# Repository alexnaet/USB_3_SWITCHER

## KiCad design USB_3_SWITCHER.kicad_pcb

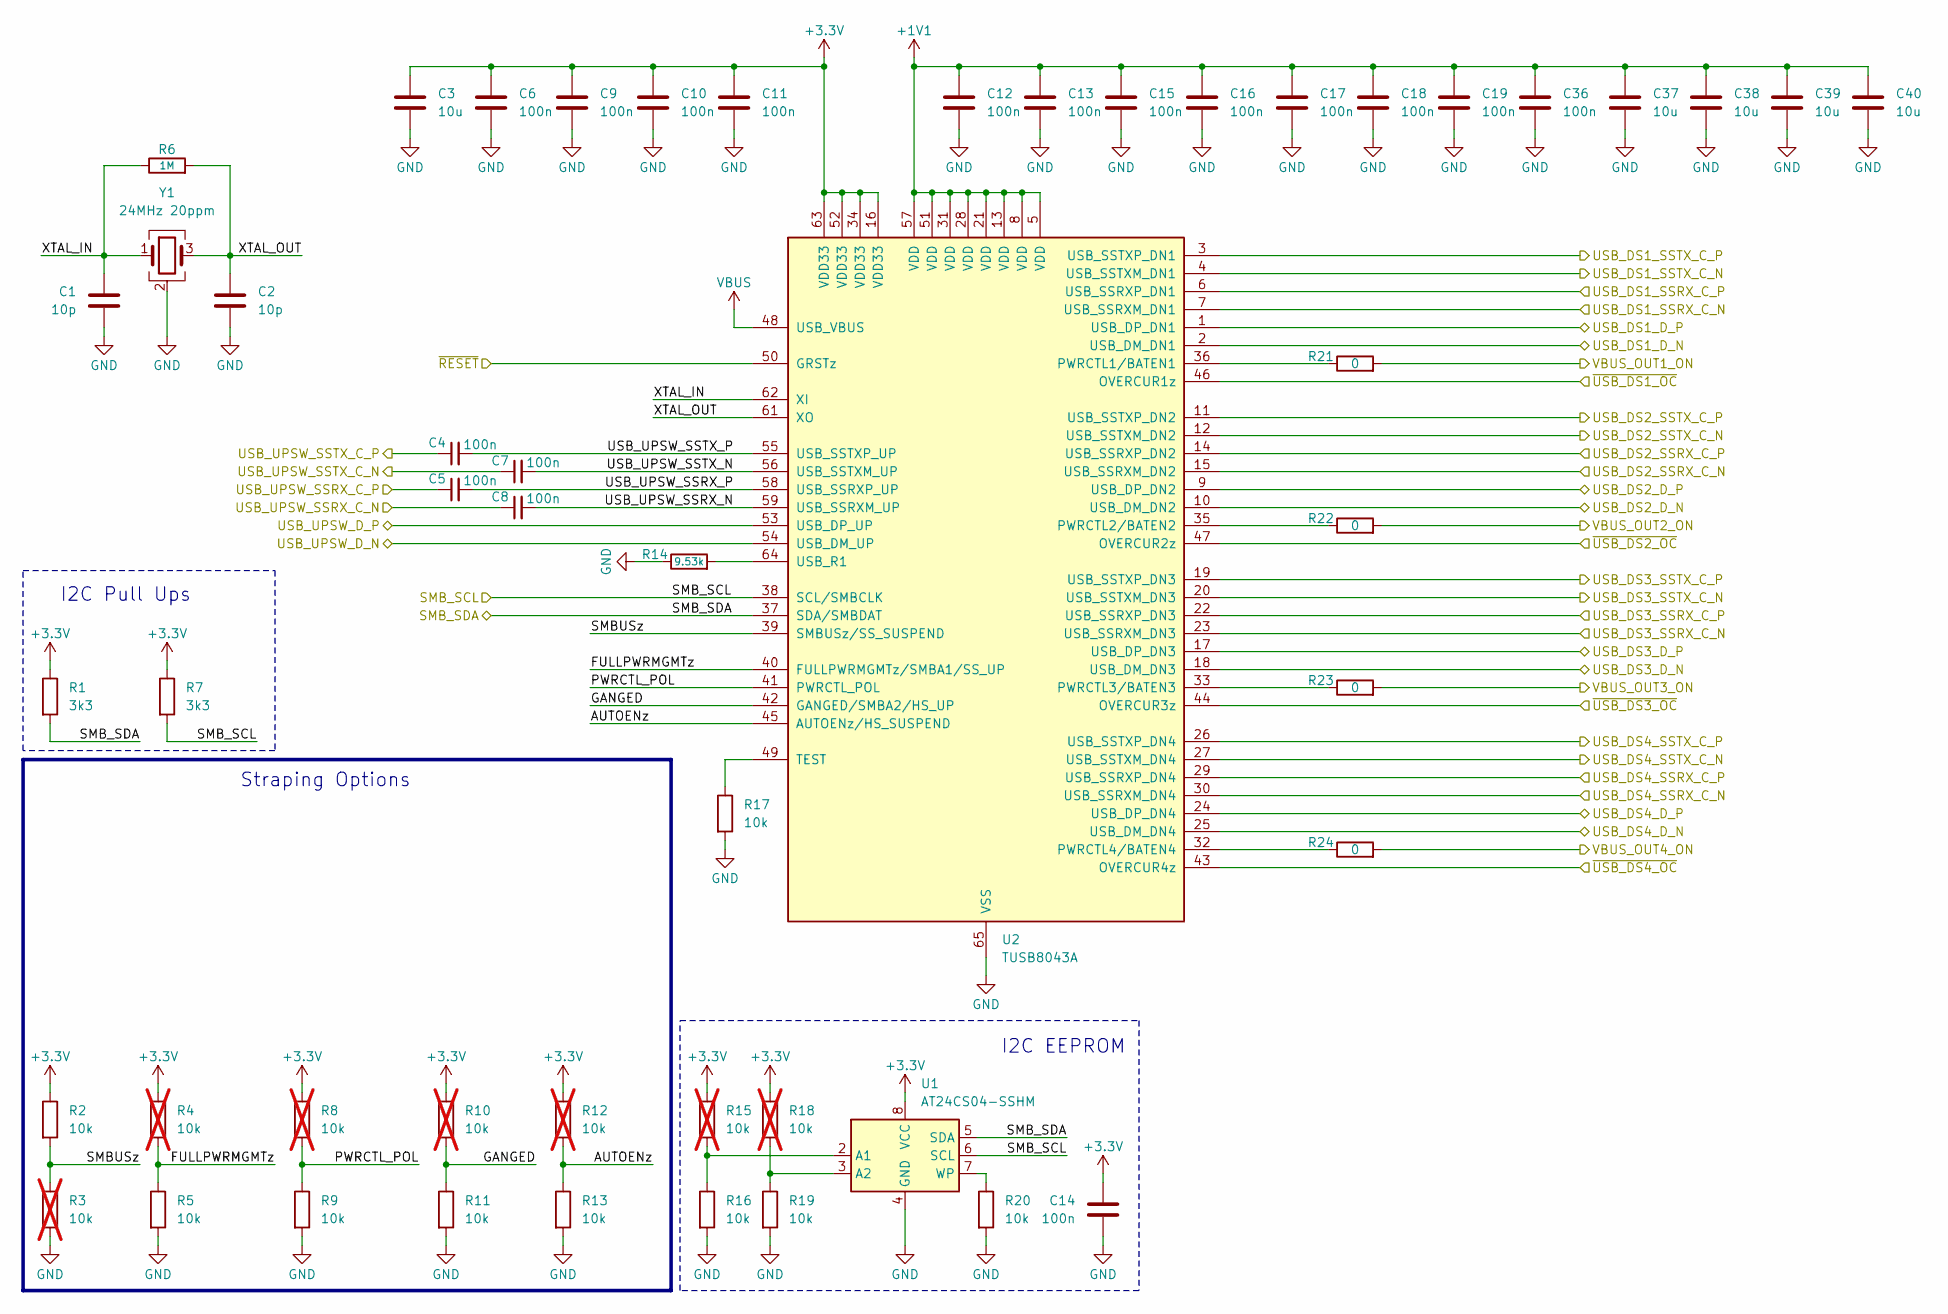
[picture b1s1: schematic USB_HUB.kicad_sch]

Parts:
C1, C2: 10p; Cap_0402
C3, C37, C38, C39, C40: 10u; Cap_0603
C4, C5, C6, C7, C8, C9, C10, C11, C12, C13, C14, C15, C16, C17, C18, C19, C36: 100n; Cap_0402
R1, R7: 3k3; Res_0402
R2, R5, R9, R11, R13, R16, R17, R19, R20: 10k; Res_0402
R3, R4, R8, R10, R12, R15, R18: 10k; Res_0402; not fitted
R6: 1M; Res_0402
R14: 9.53k; Res_0402
R21, R22, R23, R24: 0; Res_0402
U1: AT24CS04-SSHM; SOIC-8_3.9x4.9mm_P1.27mm
U2: TUSB8043A; QFN-64-1EP_9x9mm_P0.5mm_EP6x6mm_ThermalVias
Y1: 24MHz 20ppm; Crystal_SMD_3225-4Pin_3.2x2.5mm

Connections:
+1V1: C12.2, C13.2, C15.2, C16.2, C17.2, C18.2, C19.2, C36.2, C37.1, C38.1, C39.1, C40.1, U2.5 (VDD), U2.8 (VDD), U2.13 (VDD), U2.21 (VDD), U2.28 (VDD), U2.31 (VDD), U2.51 (VDD), U2.57 (VDD); also elsewhere on the board
+3.3V: C3.1, C6.2, C9.2, C10.2, C11.2, C14.2, R1.1, R2.1, R4.1, R7.1, R8.1, R10.1, R12.1, R15.1, R18.1, U1.8 (VCC), U2.16 (VDD33), U2.34 (VDD33), U2.52 (VDD33), U2.63 (VDD33); also elsewhere on the board
/DIRECTION_SWITCH/~RESET: U2.50 (GRSTz); also elsewhere on the board
/DOWNSTREAM_CONNECTORS1/USB_DS_D_N: U2.10 (USB_DM_DN2); also elsewhere on the board
/DOWNSTREAM_CONNECTORS1/USB_DS_D_P: U2.9 (USB_DP_DN2); also elsewhere on the board
/DOWNSTREAM_CONNECTORS1/USB_DS_SSRX_C_N: U2.15 (USB_SSRXM_DN2); also elsewhere on the board
/DOWNSTREAM_CONNECTORS1/USB_DS_SSRX_C_P: U2.14 (USB_SSRXP_DN2); also elsewhere on the board
/DOWNSTREAM_CONNECTORS1/USB_DS_SSTX_C_N: U2.12 (USB_SSTXM_DN2); also elsewhere on the board
/DOWNSTREAM_CONNECTORS1/USB_DS_SSTX_C_P: U2.11 (USB_SSTXP_DN2); also elsewhere on the board
/DOWNSTREAM_CONNECTORS1/VBUS_OUT_ON: R22.2; also elsewhere on the board
/DOWNSTREAM_CONNECTORS1/~USB_DS_OC: U2.47 (OVERCUR2z); also elsewhere on the board
/DOWNSTREAM_CONNECTORS2/USB_DS_D_N: U2.18 (USB_DM_DN3); also elsewhere on the board
/DOWNSTREAM_CONNECTORS2/USB_DS_D_P: U2.17 (USB_DP_DN3); also elsewhere on the board
/DOWNSTREAM_CONNECTORS2/USB_DS_SSRX_C_N: U2.23 (USB_SSRXM_DN3); also elsewhere on the board
/DOWNSTREAM_CONNECTORS2/USB_DS_SSRX_C_P: U2.22 (USB_SSRXP_DN3); also elsewhere on the board
/DOWNSTREAM_CONNECTORS2/USB_DS_SSTX_C_N: U2.20 (USB_SSTXM_DN3); also elsewhere on the board
/DOWNSTREAM_CONNECTORS2/USB_DS_SSTX_C_P: U2.19 (USB_SSTXP_DN3); also elsewhere on the board
/DOWNSTREAM_CONNECTORS2/VBUS_OUT_ON: R23.2; also elsewhere on the board
/DOWNSTREAM_CONNECTORS2/~USB_DS_OC: U2.44 (OVERCUR3z); also elsewhere on the board
/DOWNSTREAM_CONNECTORS3/USB_DS_D_N: U2.25 (USB_DM_DN4); also elsewhere on the board
/DOWNSTREAM_CONNECTORS3/USB_DS_D_P: U2.24 (USB_DP_DN4); also elsewhere on the board
/DOWNSTREAM_CONNECTORS3/USB_DS_SSRX_C_N: U2.30 (USB_SSRXM_DN4); also elsewhere on the board
/DOWNSTREAM_CONNECTORS3/USB_DS_SSRX_C_P: U2.29 (USB_SSRXP_DN4); also elsewhere on the board
/DOWNSTREAM_CONNECTORS3/USB_DS_SSTX_C_N: U2.27 (USB_SSTXM_DN4); also elsewhere on the board
/DOWNSTREAM_CONNECTORS3/USB_DS_SSTX_C_P: U2.26 (USB_SSTXP_DN4); also elsewhere on the board
/DOWNSTREAM_CONNECTORS3/VBUS_OUT_ON: R24.2; also elsewhere on the board
/DOWNSTREAM_CONNECTORS3/~USB_DS_OC: U2.43 (OVERCUR4z); also elsewhere on the board
/DOWNSTREAM_CONNECTORS/USB_DS_D_N: U2.2 (USB_DM_DN1); also elsewhere on the board
/DOWNSTREAM_CONNECTORS/USB_DS_D_P: U2.1 (USB_DP_DN1); also elsewhere on the board
/DOWNSTREAM_CONNECTORS/USB_DS_SSRX_C_N: U2.7 (USB_SSRXM_DN1); also elsewhere on the board
/DOWNSTREAM_CONNECTORS/USB_DS_SSRX_C_P: U2.6 (USB_SSRXP_DN1); also elsewhere on the board
/DOWNSTREAM_CONNECTORS/USB_DS_SSTX_C_N: U2.4 (USB_SSTXM_DN1); also elsewhere on the board
/DOWNSTREAM_CONNECTORS/USB_DS_SSTX_C_P: U2.3 (USB_SSTXP_DN1); also elsewhere on the board
/DOWNSTREAM_CONNECTORS/VBUS_OUT_ON: R21.2; also elsewhere on the board
/DOWNSTREAM_CONNECTORS/~USB_DS_OC: U2.46 (OVERCUR1z); also elsewhere on the board
/HS_MUX/USB_UPSW_D_N: U2.54 (USB_DM_UP); also elsewhere on the board
/HS_MUX/USB_UPSW_D_P: U2.53 (USB_DP_UP); also elsewhere on the board
/HS_MUX/USB_UPSW_SSRX_C_N: C8.1; also elsewhere on the board
/HS_MUX/USB_UPSW_SSRX_C_P: C5.1; also elsewhere on the board
/HS_MUX/USB_UPSW_SSTX_C_N: C7.1; also elsewhere on the board
/HS_MUX/USB_UPSW_SSTX_C_P: C4.1; also elsewhere on the board
/USB_HUB/AUTOENz: R12.2, R13.1, U2.45 (AUTOENz/HS_SUSPEND)
/USB_HUB/FULLPWRMGMTz: R4.2, R5.1, U2.40 (FULLPWRMGMTz/SMBA1/SS_UP)
/USB_HUB/GANGED: R10.2, R11.1, U2.42 (GANGED/SMBA2/HS_UP)
/USB_HUB/PWRCTL_POL: R8.2, R9.1, U2.41 (PWRCTL_POL)
/USB_HUB/SMBUSz: R2.2, R3.1, U2.39 (SMBUSz/SS_SUSPEND)
/USB_HUB/SMB_SCL: R7.2, U1.6 (SCL), U2.38 (SCL/SMBCLK); also elsewhere on the board
/USB_HUB/SMB_SDA: R1.2, U1.5 (SDA), U2.37 (SDA/SMBDAT); also elsewhere on the board
/USB_HUB/USB_UPSW_SSRX_N: C8.2, U2.59 (USB_SSRXM_UP)
/USB_HUB/USB_UPSW_SSRX_P: C5.2, U2.58 (USB_SSRXP_UP)
/USB_HUB/USB_UPSW_SSTX_N: C7.2, U2.56 (USB_SSTXM_UP)
/USB_HUB/USB_UPSW_SSTX_P: C4.2, U2.55 (USB_SSTXP_UP)
/USB_HUB/XTAL_IN: C1.2, R6.1, U2.62 (XI), Y1.1
/USB_HUB/XTAL_OUT: C2.2, R6.2, U2.61 (XO), Y1.3
GND: C1.1, C2.1, C3.2, C6.1, C9.1, C10.1, C11.1, C12.1, C13.1, C14.1, C15.1, C16.1, C17.1, C18.1, C19.1, C36.1, C37.2, C38.2, C39.2, C40.2, R3.2, R5.2, R9.2, R11.2, R13.2, R14.1, R16.2, R17.2, R19.2, R20.2, U1.4 (GND), U2.65 (VSS), Y1.2 (G), Y1.4 (G); also elsewhere on the board
unnamed: R15.2, R16.1, U1.2 (A1)
unnamed: R18.2, R19.1, U1.3 (A2)
unnamed: R20.1, U1.7 (WP)
unnamed: R21.1, U2.36 (PWRCTL1/BATEN1)
unnamed: R22.1, U2.35 (PWRCTL2/BATEN2)
unnamed: R23.1, U2.33 (PWRCTL3/BATEN3)
unnamed: R24.1, U2.32 (PWRCTL4/BATEN4)
unnamed: R17.1, U2.49 (TEST)
unnamed: R14.2, U2.64 (USB_R1)
VBUS: U2.48 (USB_VBUS); also elsewhere on the board

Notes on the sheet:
Straping Options
I2C Pull Ups
I2C EEPROM

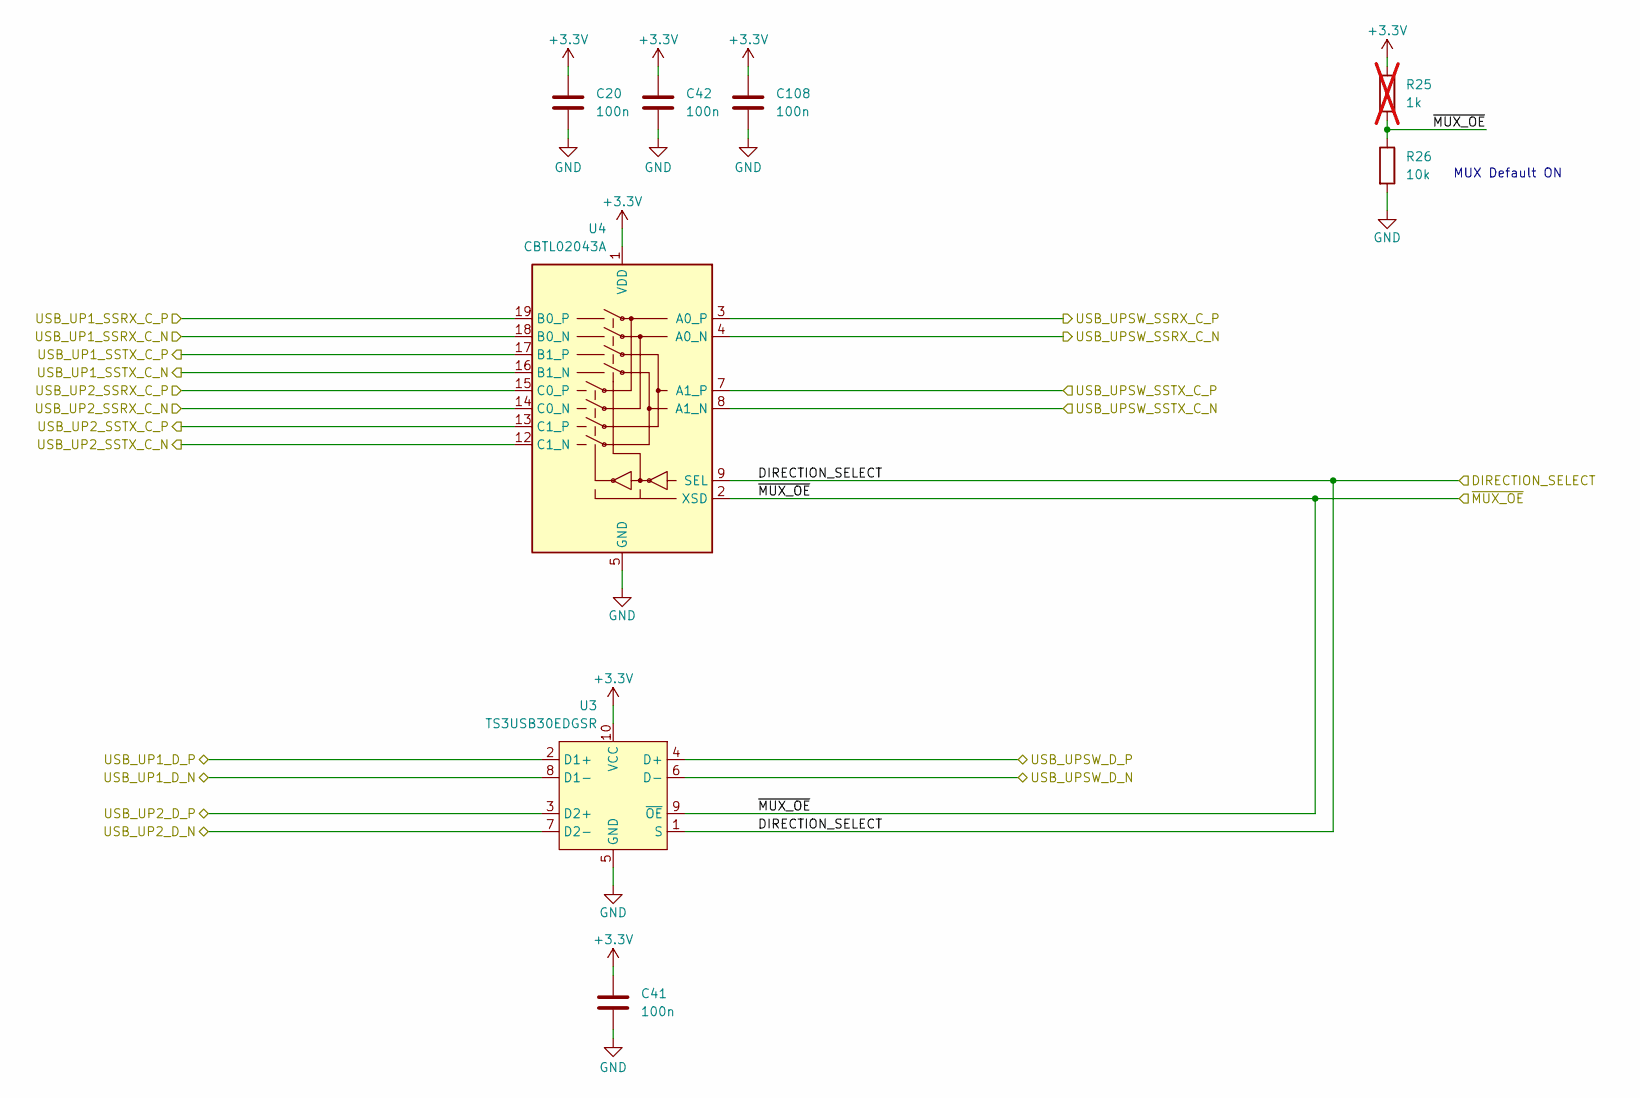
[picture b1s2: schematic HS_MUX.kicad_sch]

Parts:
C20, C41, C42, C108: 100n; Cap_0402
R25: 1k; Res_0402; not fitted
R26: 10k; Res_0402
U3: TS3USB30EDGSR; HVSSOP-10-1EP_3x3mm_P0.5mm_EP1.83x1.89mm
U4: CBTL02043A; WQFN-20-1EP_2.5x4.5mm_P0.5mm_EP1x2.9mm

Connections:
+3.3V: C20.2, C41.2, C42.2, C108.2, R25.1, U3.10 (VCC), U4.1 (VDD), U4.6 (VDD), U4.10 (VDD); also elsewhere on the board
/HS_MUX/DIRECTION_SELECT: U3.1 (S), U4.9 (SEL); also elsewhere on the board
/HS_MUX/USB_UP1_SSRX_C_N: U4.18 (B0_N); also elsewhere on the board
/HS_MUX/USB_UP1_SSRX_C_P: U4.19 (B0_P); also elsewhere on the board
/HS_MUX/USB_UP1_SSTX_C_N: U4.16 (B1_N); also elsewhere on the board
/HS_MUX/USB_UP1_SSTX_C_P: U4.17 (B1_P); also elsewhere on the board
/HS_MUX/USB_UP2_SSRX_C_N: U4.14 (C0_N); also elsewhere on the board
/HS_MUX/USB_UP2_SSRX_C_P: U4.15 (C0_P); also elsewhere on the board
/HS_MUX/USB_UP2_SSTX_C_N: U4.12 (C1_N); also elsewhere on the board
/HS_MUX/USB_UP2_SSTX_C_P: U4.13 (C1_P); also elsewhere on the board
/HS_MUX/USB_UPSW_D_N: U3.6 (D-); also elsewhere on the board
/HS_MUX/USB_UPSW_D_P: U3.4 (D+); also elsewhere on the board
/HS_MUX/USB_UPSW_SSRX_C_N: U4.4 (A0_N); also elsewhere on the board
/HS_MUX/USB_UPSW_SSRX_C_P: U4.3 (A0_P); also elsewhere on the board
/HS_MUX/USB_UPSW_SSTX_C_N: U4.8 (A1_N); also elsewhere on the board
/HS_MUX/USB_UPSW_SSTX_C_P: U4.7 (A1_P); also elsewhere on the board
/HS_MUX/~MUX_OE: R25.2, R26.1, U3.9 (~OE), U4.2 (XSD); also elsewhere on the board
/UPSTREAM_CON1/USB_UP_D_N: U3.7 (D2-); also elsewhere on the board
/UPSTREAM_CON1/USB_UP_D_P: U3.3 (D2+); also elsewhere on the board
/UPSTREAM_CON/USB_UP_D_N: U3.8 (D1-); also elsewhere on the board
/UPSTREAM_CON/USB_UP_D_P: U3.2 (D1+); also elsewhere on the board
GND: C20.1, C41.1, C42.1, C108.1, R26.2, U3.5 (GND), U4.5 (GND), U4.11 (GND), U4.20 (GND), U4.21 (GND); also elsewhere on the board

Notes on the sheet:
MUX Default ON

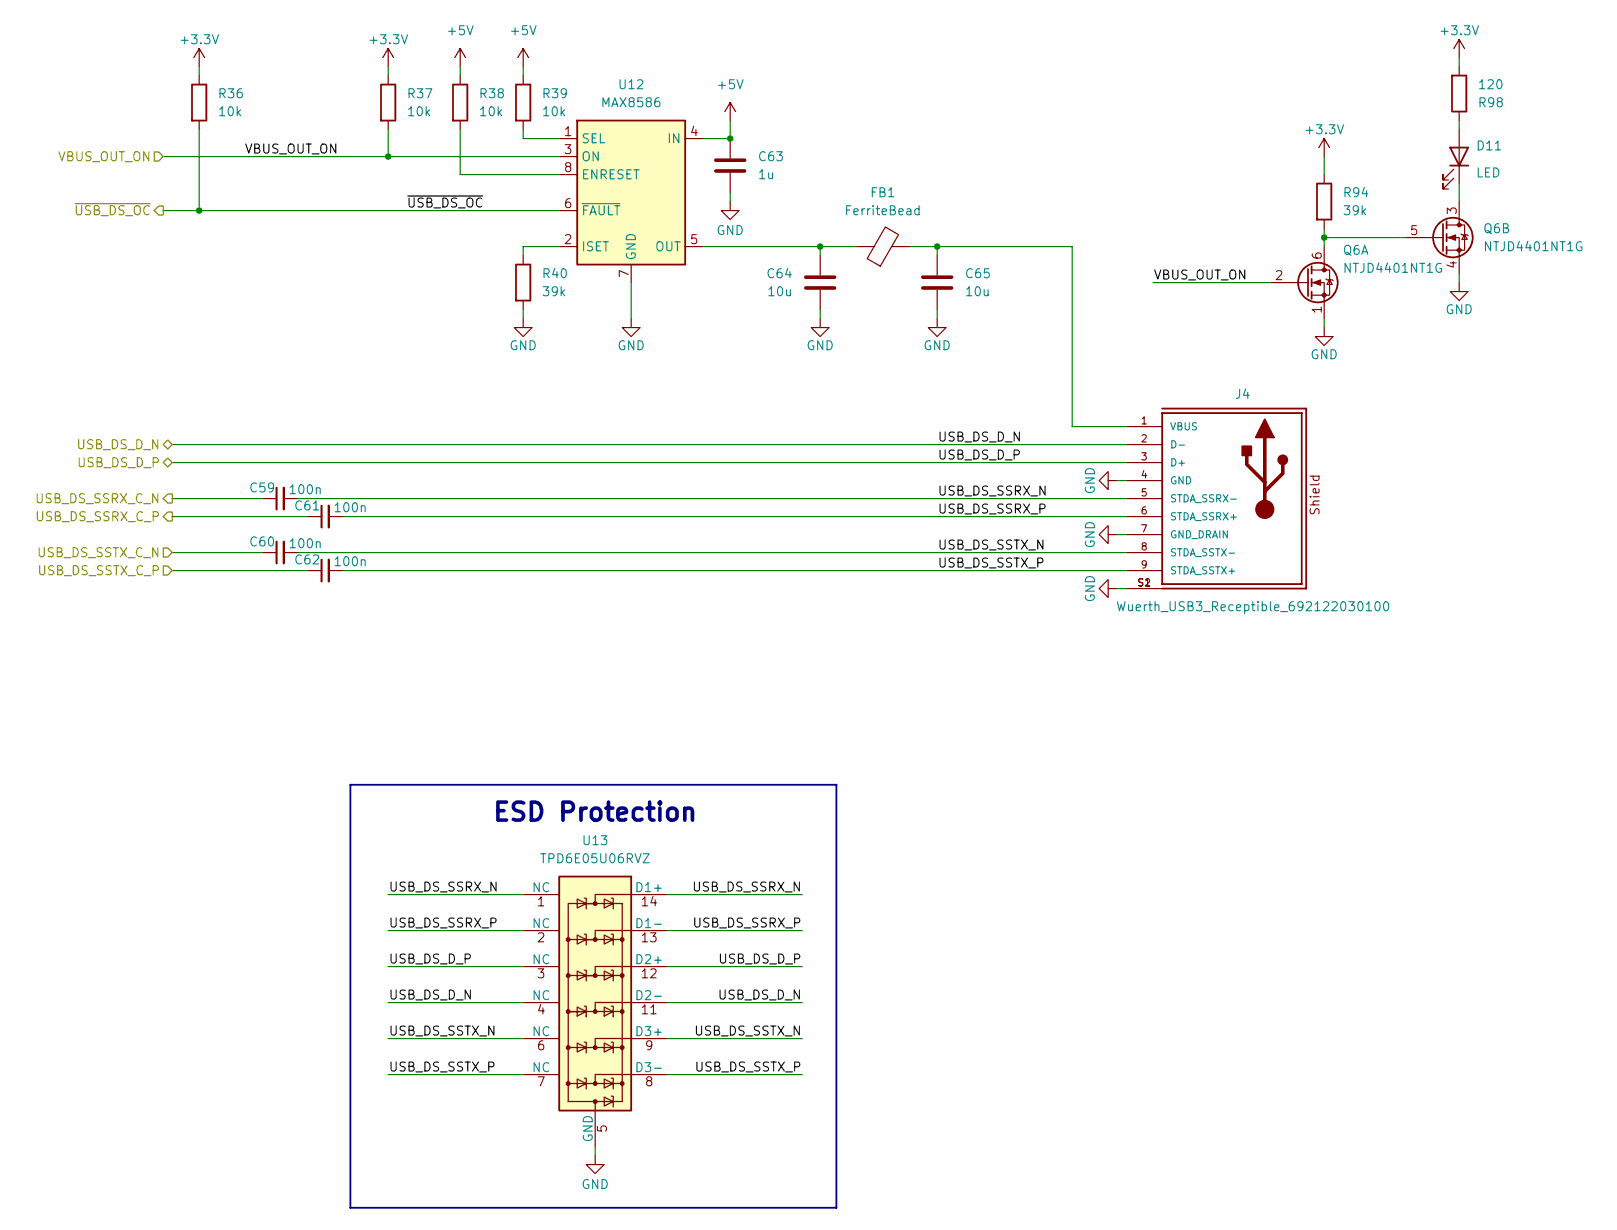
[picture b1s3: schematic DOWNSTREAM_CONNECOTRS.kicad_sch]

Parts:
C59, C60, C61, C62: 100n; Cap_0402
C63: 1u; Cap_0402
C64, C65: 10u; Cap_0603
D11: LED; LED_D3.0mm_Horizontal_O6.35mm_Z2.0mm
FB1: FerriteBead; R_0805_2012Metric
J4: Wuerth_USB3_Receptible_692122030100; Wuerth_USB3A_receptible_692122030100; DigiKey_Part_Number 732-3150-1-ND
Q6: NTJD4401NT1G; SOT-363_SC-70-6
R36, R37, R38, R39: 10k; Res_0402
R40, R94: 39k; Res_0402
R98: 120; Res_0402
U12: MAX8586; DFN-8-1EP_3x3mm_P0.65mm_EP1.55x2.4mm
U13: TPD6E05U06RVZ; Texas_R-PUSON-N14

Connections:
+3.3V: R36.1, R37.1, R94.1, R98.2; also elsewhere on the board
+5V: C63.2, R38.1, R39.1, U12.4 (IN); also elsewhere on the board
/DOWNSTREAM_CONNECTORS/USB_DS_D_N: J4.2 (D-), U13.4 (NC), U13.11 (D2-); also elsewhere on the board
/DOWNSTREAM_CONNECTORS/USB_DS_D_P: J4.3 (D+), U13.3 (NC), U13.12 (D2+); also elsewhere on the board
/DOWNSTREAM_CONNECTORS/USB_DS_SSRX_C_N: C59.1; also elsewhere on the board
/DOWNSTREAM_CONNECTORS/USB_DS_SSRX_C_P: C61.1; also elsewhere on the board
/DOWNSTREAM_CONNECTORS/USB_DS_SSRX_N: C59.2, J4.5 (STDA_SSRX-), U13.1 (NC), U13.14 (D1+)
/DOWNSTREAM_CONNECTORS/USB_DS_SSRX_P: C61.2, J4.6 (STDA_SSRX+), U13.2 (NC), U13.13 (D1-)
/DOWNSTREAM_CONNECTORS/USB_DS_SSTX_C_N: C60.1; also elsewhere on the board
/DOWNSTREAM_CONNECTORS/USB_DS_SSTX_C_P: C62.1; also elsewhere on the board
/DOWNSTREAM_CONNECTORS/USB_DS_SSTX_N: C60.2, J4.8 (STDA_SSTX-), U13.6 (NC), U13.9 (D3+)
/DOWNSTREAM_CONNECTORS/USB_DS_SSTX_P: C62.2, J4.9 (STDA_SSTX+), U13.7 (NC), U13.8 (D3-)
/DOWNSTREAM_CONNECTORS/VBUS_OUT_ON: Q6.2 (G), R37.2, U12.3 (ON); also elsewhere on the board
/DOWNSTREAM_CONNECTORS/~USB_DS_OC: R36.2, U12.6 (~FAULT); also elsewhere on the board
GND: C63.1, C64.1, C65.2, J4.4 (GND), J4.7 (GND_DRAIN), J4.S1, J4.S2, Q6.1 (S), Q6.4 (S), R40.2, U12.7 (GND), U12.9 (GND), U13.5 (GND), U13.10 (GND); also elsewhere on the board
unnamed: D11.2 (A), R98.1
unnamed: D11.1 (K), Q6.3 (D)
unnamed: C65.1, FB1.2, J4.1 (VBUS)
unnamed: Q6.5 (G), Q6.6 (D), R94.2
unnamed: R38.2, U12.8 (ENRESET)
unnamed: R40.1, U12.2 (ISET)
unnamed: C64.2, FB1.1, U12.5 (OUT)
unnamed: R39.2, U12.1 (SEL)

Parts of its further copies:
C66, C67, C68, C69, C73, C74, C75, C76, C80, C81, C82, C83: 100n; Cap_0402
C70, C77, C84: 1u; Cap_0402
C71, C72, C78, C79, C85, C86: 10u; Cap_0603
D12, D13, D14: LED; LED_D3.0mm_Horizontal_O6.35mm_Z2.0mm
FB2, FB3, FB4: FerriteBead; R_0805_2012Metric
J5, J6, J7: Wuerth_USB3_Receptible_692122030100; Wuerth_USB3A_receptible_692122030100; DigiKey_Part_Number 732-3150-1-ND
Q7, Q8, Q9: NTJD4401NT1G; SOT-363_SC-70-6
R41, R42, R43, R44, R46, R47, R48, R49, R51, R52, R53, R54: 10k; Res_0402
R45, R50, R55, R95, R96, R97: 39k; Res_0402
R99, R100, R101: 120; Res_0402
U14, U16, U18: MAX8586; DFN-8-1EP_3x3mm_P0.65mm_EP1.55x2.4mm
U15, U17, U19: TPD6E05U06RVZ; Texas_R-PUSON-N14

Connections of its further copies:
+3.3V: R41.1, R42.1, R46.1, R47.1, R51.1, R52.1, R95.1, R96.1, R97.1, R99.2, R100.2, R101.2; also elsewhere on the board
+5V: C70.2, C77.2, C84.2, R43.1, R44.1, R48.1, R49.1, R53.1, R54.1, U14.4 (IN), U16.4 (IN), U18.4 (IN); also elsewhere on the board
/DOWNSTREAM_CONNECTORS1/USB_DS_D_N: J5.2 (D-), U15.4 (NC), U15.11 (D2-); also elsewhere on the board
/DOWNSTREAM_CONNECTORS1/USB_DS_D_P: J5.3 (D+), U15.3 (NC), U15.12 (D2+); also elsewhere on the board
/DOWNSTREAM_CONNECTORS1/USB_DS_SSRX_C_N: C66.1; also elsewhere on the board
/DOWNSTREAM_CONNECTORS1/USB_DS_SSRX_C_P: C68.1; also elsewhere on the board
/DOWNSTREAM_CONNECTORS1/USB_DS_SSRX_N: C66.2, J5.5 (STDA_SSRX-), U15.1 (NC), U15.14 (D1+)
/DOWNSTREAM_CONNECTORS1/USB_DS_SSRX_P: C68.2, J5.6 (STDA_SSRX+), U15.2 (NC), U15.13 (D1-)
/DOWNSTREAM_CONNECTORS1/USB_DS_SSTX_C_N: C67.1; also elsewhere on the board
/DOWNSTREAM_CONNECTORS1/USB_DS_SSTX_C_P: C69.1; also elsewhere on the board
/DOWNSTREAM_CONNECTORS1/USB_DS_SSTX_N: C67.2, J5.8 (STDA_SSTX-), U15.6 (NC), U15.9 (D3+)
/DOWNSTREAM_CONNECTORS1/USB_DS_SSTX_P: C69.2, J5.9 (STDA_SSTX+), U15.7 (NC), U15.8 (D3-)
/DOWNSTREAM_CONNECTORS1/VBUS_OUT_ON: Q7.2 (G), R42.2, U14.3 (ON); also elsewhere on the board
/DOWNSTREAM_CONNECTORS1/~USB_DS_OC: R41.2, U14.6 (~FAULT); also elsewhere on the board
/DOWNSTREAM_CONNECTORS2/USB_DS_D_N: J6.2 (D-), U17.4 (NC), U17.11 (D2-); also elsewhere on the board
/DOWNSTREAM_CONNECTORS2/USB_DS_D_P: J6.3 (D+), U17.3 (NC), U17.12 (D2+); also elsewhere on the board
/DOWNSTREAM_CONNECTORS2/USB_DS_SSRX_C_N: C73.1; also elsewhere on the board
/DOWNSTREAM_CONNECTORS2/USB_DS_SSRX_C_P: C75.1; also elsewhere on the board
/DOWNSTREAM_CONNECTORS2/USB_DS_SSRX_N: C73.2, J6.5 (STDA_SSRX-), U17.1 (NC), U17.14 (D1+)
/DOWNSTREAM_CONNECTORS2/USB_DS_SSRX_P: C75.2, J6.6 (STDA_SSRX+), U17.2 (NC), U17.13 (D1-)
/DOWNSTREAM_CONNECTORS2/USB_DS_SSTX_C_N: C74.1; also elsewhere on the board
/DOWNSTREAM_CONNECTORS2/USB_DS_SSTX_C_P: C76.1; also elsewhere on the board
/DOWNSTREAM_CONNECTORS2/USB_DS_SSTX_N: C74.2, J6.8 (STDA_SSTX-), U17.6 (NC), U17.9 (D3+)
/DOWNSTREAM_CONNECTORS2/USB_DS_SSTX_P: C76.2, J6.9 (STDA_SSTX+), U17.7 (NC), U17.8 (D3-)
/DOWNSTREAM_CONNECTORS2/VBUS_OUT_ON: Q8.2 (G), R47.2, U16.3 (ON); also elsewhere on the board
/DOWNSTREAM_CONNECTORS2/~USB_DS_OC: R46.2, U16.6 (~FAULT); also elsewhere on the board
/DOWNSTREAM_CONNECTORS3/USB_DS_D_N: J7.2 (D-), U19.4 (NC), U19.11 (D2-); also elsewhere on the board
/DOWNSTREAM_CONNECTORS3/USB_DS_D_P: J7.3 (D+), U19.3 (NC), U19.12 (D2+); also elsewhere on the board
/DOWNSTREAM_CONNECTORS3/USB_DS_SSRX_C_N: C80.1; also elsewhere on the board
/DOWNSTREAM_CONNECTORS3/USB_DS_SSRX_C_P: C82.1; also elsewhere on the board
/DOWNSTREAM_CONNECTORS3/USB_DS_SSRX_N: C80.2, J7.5 (STDA_SSRX-), U19.1 (NC), U19.14 (D1+)
/DOWNSTREAM_CONNECTORS3/USB_DS_SSRX_P: C82.2, J7.6 (STDA_SSRX+), U19.2 (NC), U19.13 (D1-)
/DOWNSTREAM_CONNECTORS3/USB_DS_SSTX_C_N: C81.1; also elsewhere on the board
/DOWNSTREAM_CONNECTORS3/USB_DS_SSTX_C_P: C83.1; also elsewhere on the board
/DOWNSTREAM_CONNECTORS3/USB_DS_SSTX_N: C81.2, J7.8 (STDA_SSTX-), U19.6 (NC), U19.9 (D3+)
/DOWNSTREAM_CONNECTORS3/USB_DS_SSTX_P: C83.2, J7.9 (STDA_SSTX+), U19.7 (NC), U19.8 (D3-)
/DOWNSTREAM_CONNECTORS3/VBUS_OUT_ON: Q9.2 (G), R52.2, U18.3 (ON); also elsewhere on the board
/DOWNSTREAM_CONNECTORS3/~USB_DS_OC: R51.2, U18.6 (~FAULT); also elsewhere on the board
GND: C70.1, C71.1, C72.2, C77.1, C78.1, C79.2, C84.1, C85.1, C86.2, J5.4 (GND), J5.7 (GND_DRAIN), J5.S1, J5.S2, J6.4 (GND), J6.7 (GND_DRAIN), J6.S1, J6.S2, J7.4 (GND), J7.7 (GND_DRAIN), J7.S1, J7.S2, Q7.1 (S), Q7.4 (S), Q8.1 (S), Q8.4 (S), Q9.1 (S), Q9.4 (S), R45.2, R50.2, R55.2, U14.7 (GND), U14.9 (GND), U15.5 (GND), U15.10 (GND), U16.7 (GND), U16.9 (GND), U17.5 (GND), U17.10 (GND), U18.7 (GND), U18.9 (GND), U19.5 (GND), U19.10 (GND); also elsewhere on the board
unnamed: D12.2 (A), R99.1
unnamed: D12.1 (K), Q7.3 (D)
unnamed: D13.2 (A), R100.1
unnamed: D13.1 (K), Q8.3 (D)
unnamed: D14.2 (A), R101.1
unnamed: D14.1 (K), Q9.3 (D)
unnamed: C72.1, FB2.2, J5.1 (VBUS)
unnamed: C79.1, FB3.2, J6.1 (VBUS)
unnamed: C86.1, FB4.2, J7.1 (VBUS)
unnamed: Q7.5 (G), Q7.6 (D), R95.2
unnamed: Q8.5 (G), Q8.6 (D), R96.2
unnamed: Q9.5 (G), Q9.6 (D), R97.2
unnamed: R43.2, U14.8 (ENRESET)
unnamed: R45.1, U14.2 (ISET)
unnamed: C71.2, FB2.1, U14.5 (OUT)
unnamed: R44.2, U14.1 (SEL)
unnamed: R48.2, U16.8 (ENRESET)
unnamed: R50.1, U16.2 (ISET)
unnamed: C78.2, FB3.1, U16.5 (OUT)
unnamed: R49.2, U16.1 (SEL)
unnamed: R53.2, U18.8 (ENRESET)
unnamed: R55.1, U18.2 (ISET)
unnamed: C85.2, FB4.1, U18.5 (OUT)
unnamed: R54.2, U18.1 (SEL)

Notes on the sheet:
ESD Protection

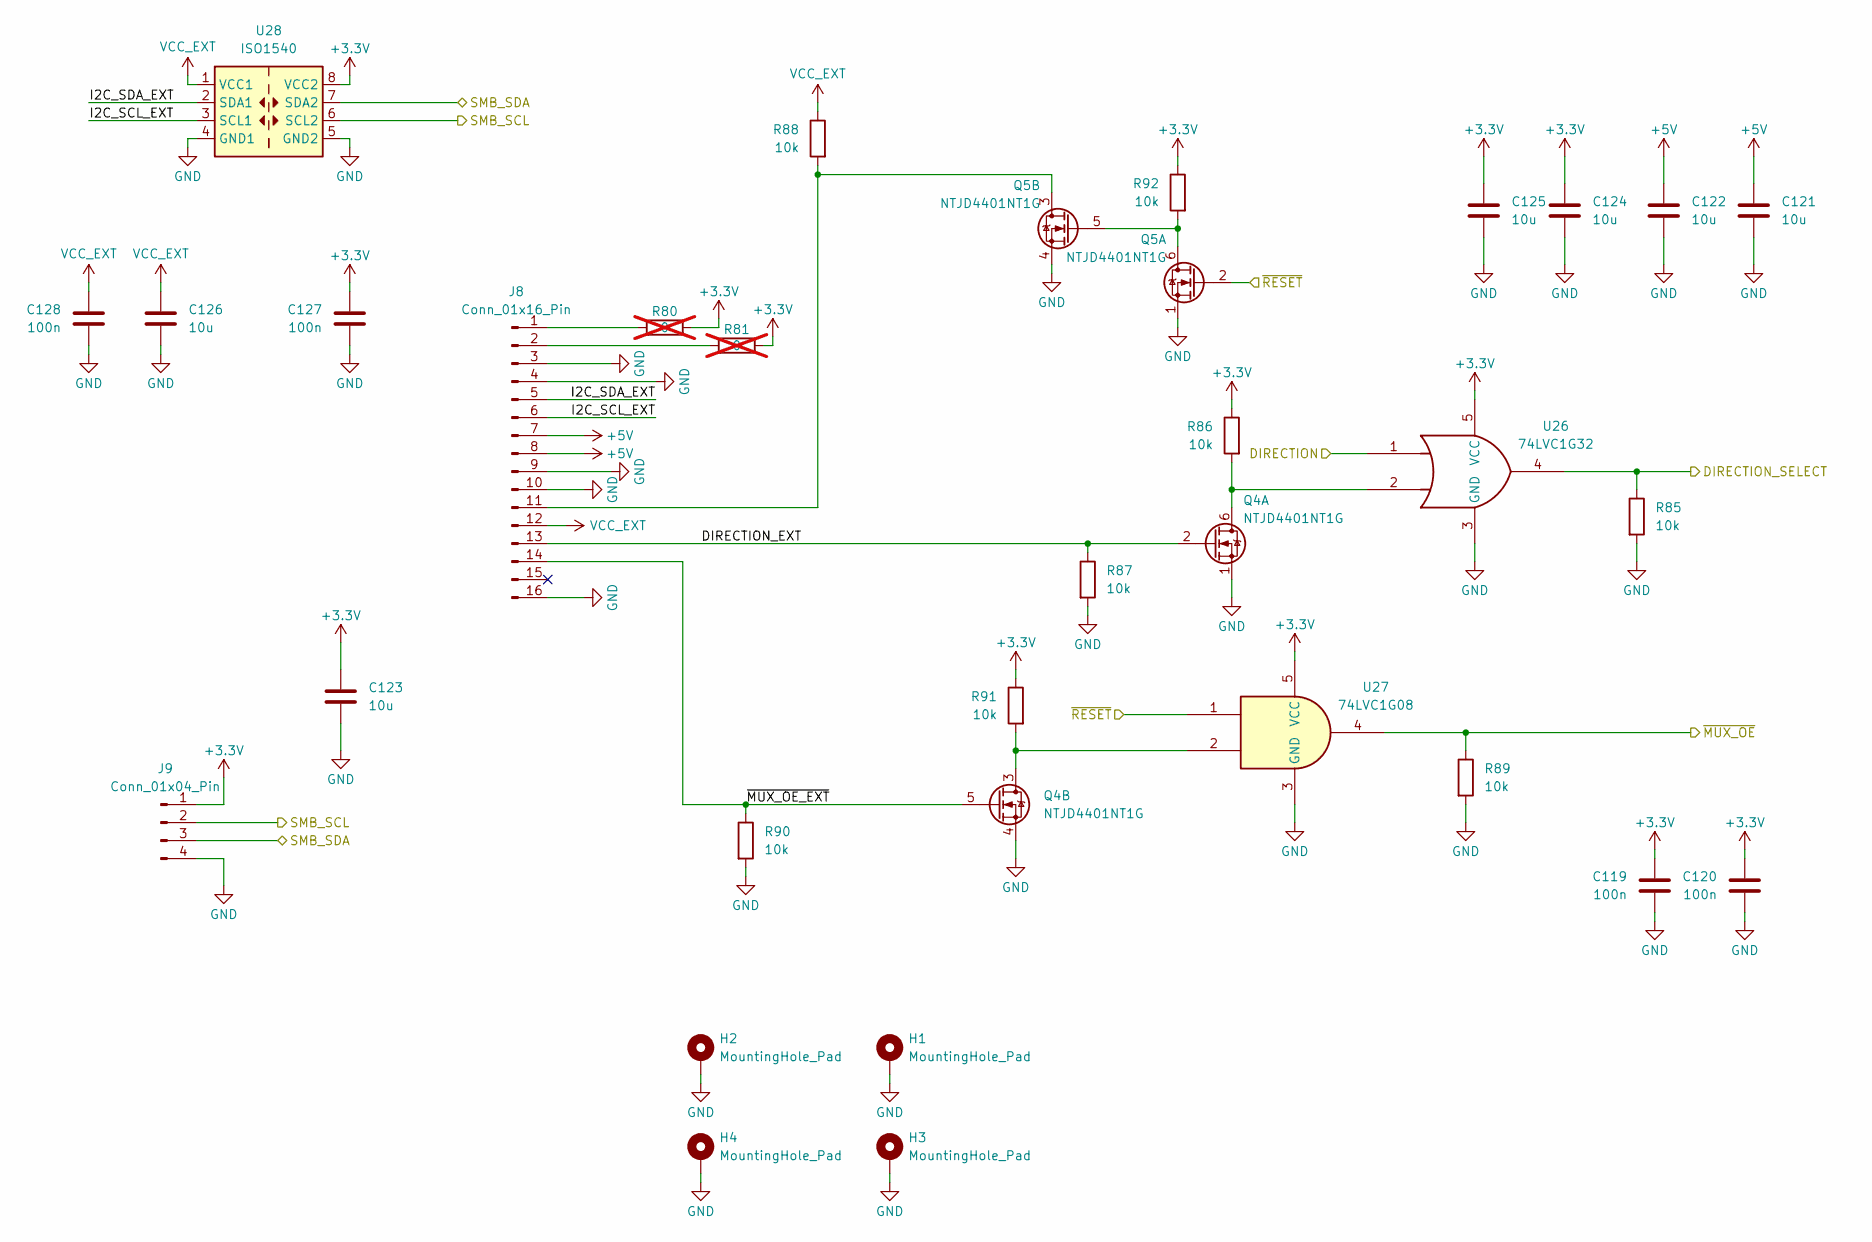
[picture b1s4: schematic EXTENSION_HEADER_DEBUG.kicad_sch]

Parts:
C119, C120, C127, C128: 100n; Cap_0402
C121, C122, C123, C124, C125, C126: 10u; Cap_0603
H1, H2, H3, H4: MountingHole_Pad; MountingHole_3.2mm_M3_Pad_TopBottom
J8: Conn_01x16_Pin; PinHeader_2x08_P2.54mm_Vertical_SMD
J9: Conn_01x04_Pin; PinHeader_1x04_P2.54mm_Vertical_SMD_Pin1Left
Q4, Q5: NTJD4401NT1G; SOT-363_SC-70-6
R80, R81: 0; Res_0603; not fitted
R85, R86, R87, R88, R89, R90, R91, R92: 10k; Res_0402
U26: 74LVC1G32; SOT-23-5
U27: 74LVC1G08; SOT-23-5
U28: ISO1540; SOIC-8_3.9x4.9mm_P1.27mm

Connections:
+3.3V: C119.1, C120.1, C123.1, C124.1, C125.1, C127.1, J9.1, R80.2, R81.2, R86.1, R91.1, R92.1, U26.5 (VCC), U27.5 (VCC), U28.8 (VCC2); also elsewhere on the board
+5V: C121.1, C122.1, J8.7, J8.8; also elsewhere on the board
/DIRECTION_SWITCH/DIRECTION: U26.1; also elsewhere on the board
/DIRECTION_SWITCH/~RESET: Q5.2 (G), U27.1; also elsewhere on the board
/EXTENSION_HEADER_DEBUG/DIRECTION_EXT: J8.13, Q4.2 (G), R87.1
/EXTENSION_HEADER_DEBUG/I2C_SCL_EXT: J8.6, U28.3 (SCL1)
/EXTENSION_HEADER_DEBUG/I2C_SDA_EXT: J8.5, U28.2 (SDA1)
/EXTENSION_HEADER_DEBUG/~MUX_OE_EXT: J8.14, Q4.5 (G), R90.1
/HS_MUX/DIRECTION_SELECT: R85.1, U26.4; also elsewhere on the board
/HS_MUX/~MUX_OE: R89.1, U27.4; also elsewhere on the board
/USB_HUB/SMB_SCL: J9.2, U28.6 (SCL2); also elsewhere on the board
/USB_HUB/SMB_SDA: J9.3, U28.7 (SDA2); also elsewhere on the board
GND: C119.2, C120.2, C121.2, C122.2, C123.2, C124.2, C125.2, C126.2, C127.2, C128.2, H1.1 (1_1), H2.1 (1_1), H3.1 (1_1), H4.1 (1_1), J8.3, J8.4, J8.9, J8.10, J8.16, J9.4, Q4.1 (S), Q4.4 (S), Q5.1 (S), Q5.4 (S), R85.2, R87.2, R89.2, R90.2, U26.3 (GND), U27.3 (GND), U28.4 (GND1), U28.5 (GND2); also elsewhere on the board
unnamed: J8.1, R80.1
unnamed: J8.2, R81.1
unnamed: J8.11, Q5.3 (D), R88.2
unnamed: Q4.6 (D), R86.2, U26.2
unnamed: Q4.3 (D), R91.2, U27.2
unnamed: Q5.5 (G), Q5.6 (D), R92.2
VCC_EXT: C126.1, C128.1, J8.12, R88.1, U28.1 (VCC1)

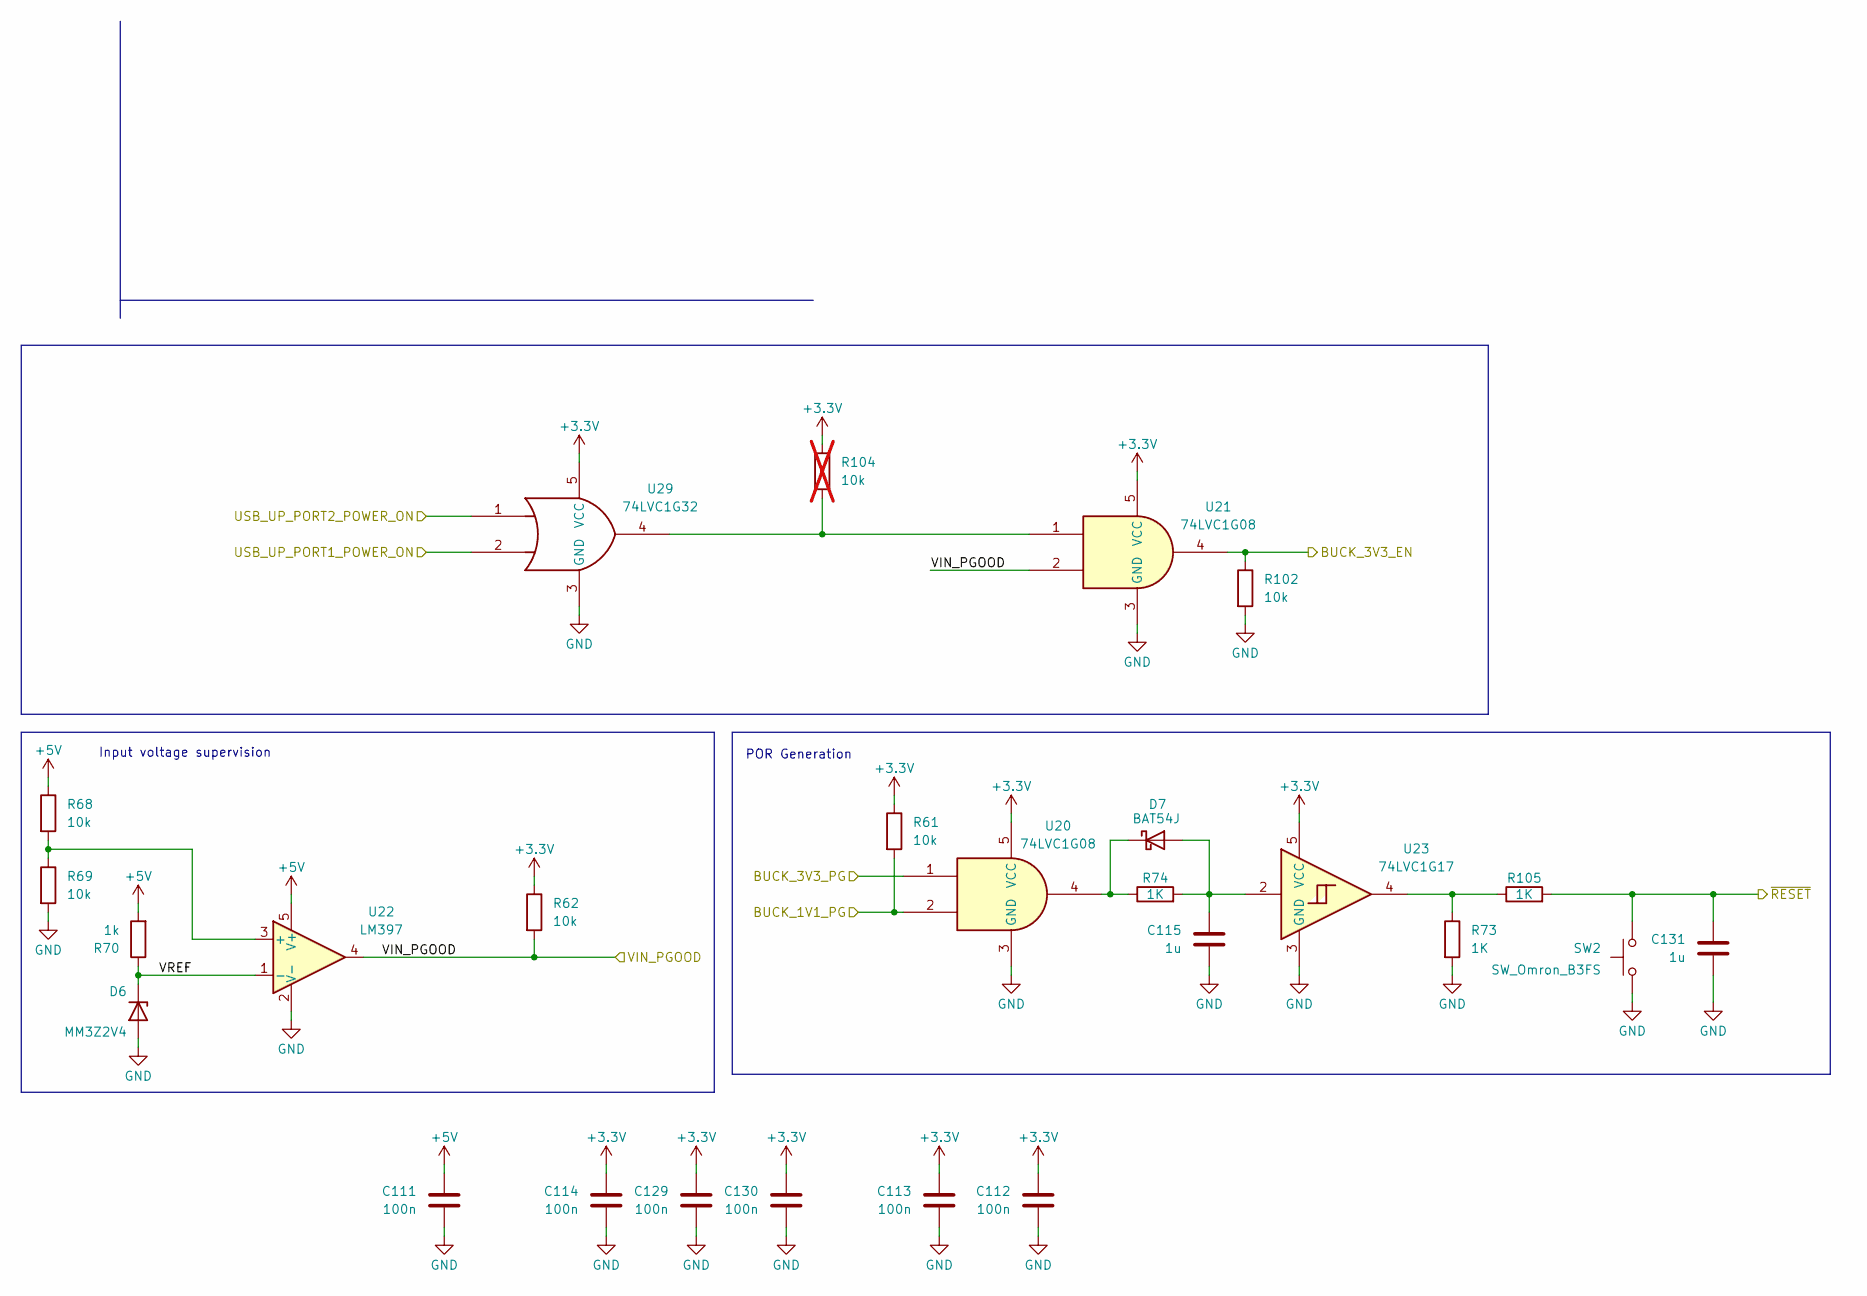
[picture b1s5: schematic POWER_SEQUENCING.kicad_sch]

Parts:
C111, C112, C113, C114, C129, C130: 100n; Cap_0402
C115, C131: 1u; Cap_0402
D6: MM3Z2V4; D_SOD-323F
D7: BAT54J; D_SOD-323F
R61, R62, R68, R69, R102: 10k; Res_0402
R70: 1k; Res_0402
R73, R74, R105: 1K; Cap_0402
R104: 10k; Res_0402; not fitted
SW2: SW_Omron_B3FS; SW_SPST_Omron_B3FS-100xP
U20, U21: 74LVC1G08; SOT-23-5
U22: LM397; SOT-23-5
U23: 74LVC1G17; SOT-23-5
U29: 74LVC1G32; SOT-23-5

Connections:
+3.3V: C112.1, C113.1, C114.1, C129.1, C130.1, R61.1, R62.1, R104.1, U20.5 (VCC), U21.5 (VCC), U23.5 (VCC), U29.5 (VCC); also elsewhere on the board
+5V: C111.1, R68.1, R70.2, U22.5 (V+); also elsewhere on the board
/DIRECTION_SWITCH/~RESET: C131.1, R105.2, SW2.2; also elsewhere on the board
/POWER_SEQUENCING/BUCK_1V1_PG: R61.2, U20.2; also elsewhere on the board
/POWER_SEQUENCING/BUCK_3V3_EN: R102.1, U21.4; also elsewhere on the board
/POWER_SEQUENCING/USB_UP_PORT1_POWER_ON: U29.2; also elsewhere on the board
/POWER_SEQUENCING/USB_UP_PORT2_POWER_ON: U29.1; also elsewhere on the board
/POWER_SEQUENCING/VIN_PGOOD: R62.2, U21.2, U22.4; also elsewhere on the board
/POWER_SEQUENCING/VREF: D6.1 (K), R70.1, U22.1 (-)
/POWER_SUPPLY/BUCK_3V3_PG: U20.1; also elsewhere on the board
GND: C111.2, C112.2, C113.2, C114.2, C115.2, C129.2, C130.2, C131.2, D6.2 (A), R69.2, R73.2, R102.2, SW2.1, U20.3 (GND), U21.3 (GND), U22.2 (V-), U23.3 (GND), U29.3 (GND); also elsewhere on the board
unnamed: C115.1, D7.2 (A), R74.2, U23.2
unnamed: D7.1 (K), R74.1, U20.4
unnamed: R104.2, U21.1, U29.4
unnamed: R73.1, R105.1, U23.4
unnamed: R68.2, R69.1, U22.3 (+)

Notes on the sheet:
POR Generation
Input voltage supervision
